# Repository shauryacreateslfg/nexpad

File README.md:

# nexpad
This was my first time working on hardware and glad i chose a macropad :) [it wasnt easy tho;) ]

# motive
i started with a hackpad because its usually every beginners first project but i didnt blindly use the guide, i worked upon adding more switches and customized functioning keys too myself,it was a hassle but i managed to do it on my OWN ;)
# nexpad's schematic and pcb
<h3>Schematic</h3>

<h3>PCB</h3>

<h3>3D view</h3>

# nexpad's Bill of Materials

| # | Part | Qty | Est. price (USD){incl. delivery} | Link |
|---|------|-----|---------------------------|------|
| 1 | Seed XIAO RP2040 | 1 | $8| https://robu.in/product/seeed-studio-xiao-rp2040-v1-0/ |
| 2 | MX-style switches(pack of 10) | 1 | $5 | https://meckeys.com/shop/accessories/keyboard-accessories/key-switches/cherry-mx-rgb-switch/ |
| 3 | 1N4148 diodes(pack of 50) | 1 | $1.72 | https://amzn.in/d/06aqwh1L |
| 4 | SK6812 MINI-E RGB LEDs | 10 | $0.226 | https://nanohertztechnologies.com/products/addressable-smd-led-sk6812mini-e-6812-ws2812-opsco |
| 5 | EC11 rotary encoder,20 mm | 1 | $3 | https://amzn.in/d/0gVF5ons |
| 6 | Encoder knob, 6mm D-shaft bore | 1 | $3 | https://3dprintshop.in/product/rotary-encoder-knob-set |
| 7 | 0.91" OLED 128x32 I2C (GND-VCC-SCL-SDA) | 1 | $4.5 | https://amzn.in/d/0hrdOsnR |
| 8 | Clear DSA keycaps(set of 5) | 2 | $1.75 | https://meckeys.com/shop/accessories/keyboard-accessories/keycaps/blank/blank-dsa-keycaps-1u/ |
| 9 | M3x16mm screws(pack of 25) | 1 | $3.13 |https://robu.in/product/easymech-ht-socket-button-head-cap-allen-bolt-m3-x-16-25-pcs/?gad_source=1&gad_campaignid=17416544847&gbraid=0AAAAADvLFWcknqAv5wyUr5iHjU1fO8vGA&gclid=Cj0KCQiAiJXYBhD_ARIsAAx2AHlxDKm8Cy3Y0g9CO__VHovhe8yq4j8NSwfvPJGNMKHT2k4CM0TFYrsaAh_LEALw_wcB|
| 10 | M3x5x4 heat-set inserts(pack of 25) | 1 | $2.3 | https://www.amazon.in/Yaocom-Threaded-Inserts-Printing-Components/dp/B0DG59PW2R |
| 11 | Custom 2-layer PCB | 1 | $27 | https://www.lioncircuits.com/quote?srsltid=AYCX9vJdAOgetnfsQttWt803HXfoI7JA8gKbzYeIGTpMUAf8BRxgDmF3 |
| 12 | 3D printed case, (base + bezel), printed by a friend | 1 | $10 | https://amzn.in/d/0f2i6nKE |
| 13 | 330 Ohm Resistor(pack of 20) | 1 | $1.7 | https://quartzcomponents.com/products/330-ohm-330-e-5-smd-resistor-0805-pack-of-20-pieces |
| 14 | Soldering Iron | 1 | $2.6 | https://www.amazon.in/Electronic-Spices-Black-Color-Soldering/dp/B0BNX3WZWJ |
| 15 | Soldering Iron Stand | 1 | $1.7 | https://amzn.in/d/0aQ20640 |
| 16 | Solder Wire 60/40, 50 g | 1 | $1.5 | https://amzn.in/d/07wNbBuL |
| 17 | Soldering Flux Paste, 15 g | 1 | $1.13 | https://amzn.in/d/0eGcyvb2 |
| 18 | Desoldering Wick, 1.5 m | 1 | $2.26 | https://www.amazon.in/UPTO-DATE-PRODUCTS-Desoldering-1-5mm-1-5Meter/dp/B0H62CXC13 |
||Total Cost (including delivery)| | $85-90||

#
made with love <3 
Shaurya

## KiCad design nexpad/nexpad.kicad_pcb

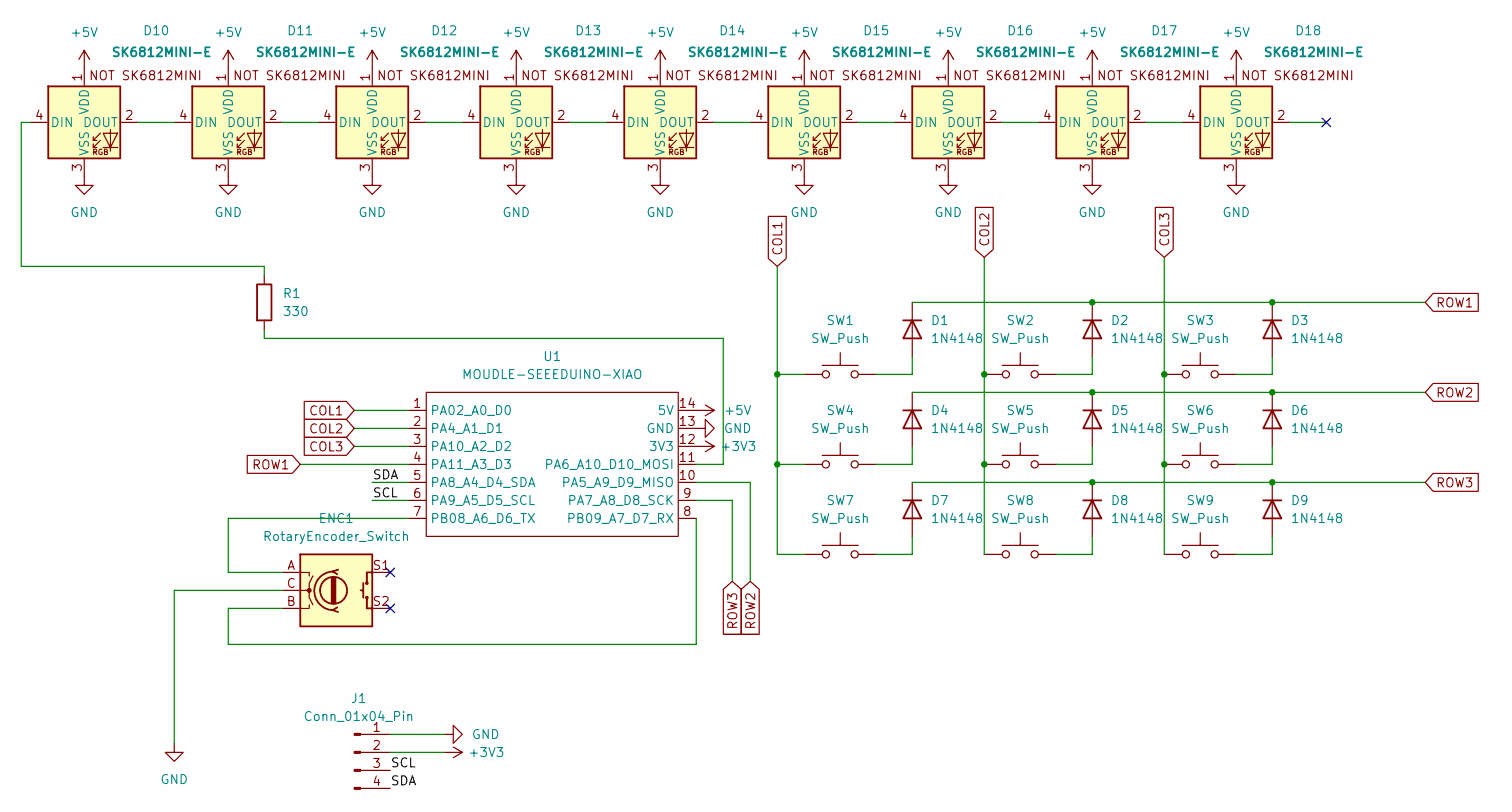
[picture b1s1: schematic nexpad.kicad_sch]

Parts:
D1, D2, D3, D4, D5, D6, D7, D8, D9: 1N4148; D_DO-35_SOD27_P7.62mm_Horizontal
D10, D11, D12, D13, D14, D15, D16, D17, D18: SK6812MINI-E; SK6812MINI-E_fixed
ENC1: RotaryEncoder_Switch; RotaryEncoder_Alps_EC11E-Switch_Vertical_H20mm
J1: Conn_01x04_Pin; SSD1306-0.91-OLED-4pin-128x32
R1: 330; R_0805_2012Metric
SW1, SW2, SW3, SW4, SW5, SW6, SW7, SW8, SW9: SW_Push; SW_Cherry_MX_1.00u_PCB
U1: MOUDLE-SEEEDUINO-XIAO; XIAO-Generic-Hybrid-14P-2.54-21X17.8MM

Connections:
+3V3: J1.2, U1.12 (3V3)
+5V: D10.1 (VDD), D11.1 (VDD), D12.1 (VDD), D13.1 (VDD), D14.1 (VDD), D15.1 (VDD), D16.1 (VDD), D17.1 (VDD), D18.1 (VDD), U1.14 (5V)
/SCL: J1.3, U1.6 (PA9_A5_D5_SCL)
/SDA: J1.4, U1.5 (PA8_A4_D4_SDA)
COL1: SW1.1, SW4.1, SW7.1, U1.1 (PA02_A0_D0)
COL2: SW2.1, SW5.1, SW8.1, U1.2 (PA4_A1_D1)
COL3: SW3.1, SW6.1, SW9.1, U1.3 (PA10_A2_D2)
GND: D10.3 (VSS), D11.3 (VSS), D12.3 (VSS), D13.3 (VSS), D14.3 (VSS), D15.3 (VSS), D16.3 (VSS), D17.3 (VSS), D18.3 (VSS), ENC1.C, J1.1, U1.13 (GND)
unnamed: D1.2 (A), SW1.2
unnamed: D2.2 (A), SW2.2
unnamed: D3.2 (A), SW3.2
unnamed: D4.2 (A), SW4.2
unnamed: D5.2 (A), SW5.2
unnamed: D6.2 (A), SW6.2
unnamed: D7.2 (A), SW7.2
unnamed: D8.2 (A), SW8.2
unnamed: D9.2 (A), SW9.2
unnamed: D10.4 (DIN), R1.1
unnamed: D10.2 (DOUT), D11.4 (DIN)
unnamed: D11.2 (DOUT), D12.4 (DIN)
unnamed: D12.2 (DOUT), D13.4 (DIN)
unnamed: D13.2 (DOUT), D14.4 (DIN)
unnamed: D14.2 (DOUT), D15.4 (DIN)
unnamed: D15.2 (DOUT), D16.4 (DIN)
unnamed: D16.2 (DOUT), D17.4 (DIN)
unnamed: D17.2 (DOUT), D18.4 (DIN)
unnamed: R1.2, U1.11 (PA6_A10_D10_MOSI)
unnamed: ENC1.A, U1.7 (PB08_A6_D6_TX)
unnamed: ENC1.B, U1.8 (PB09_A7_D7_RX)
ROW1: D1.1 (K), D2.1 (K), D3.1 (K), U1.4 (PA11_A3_D3)
ROW2: D4.1 (K), D5.1 (K), D6.1 (K), U1.10 (PA5_A9_D9_MISO)
ROW3: D7.1 (K), D8.1 (K), D9.1 (K), U1.9 (PA7_A8_D8_SCK)

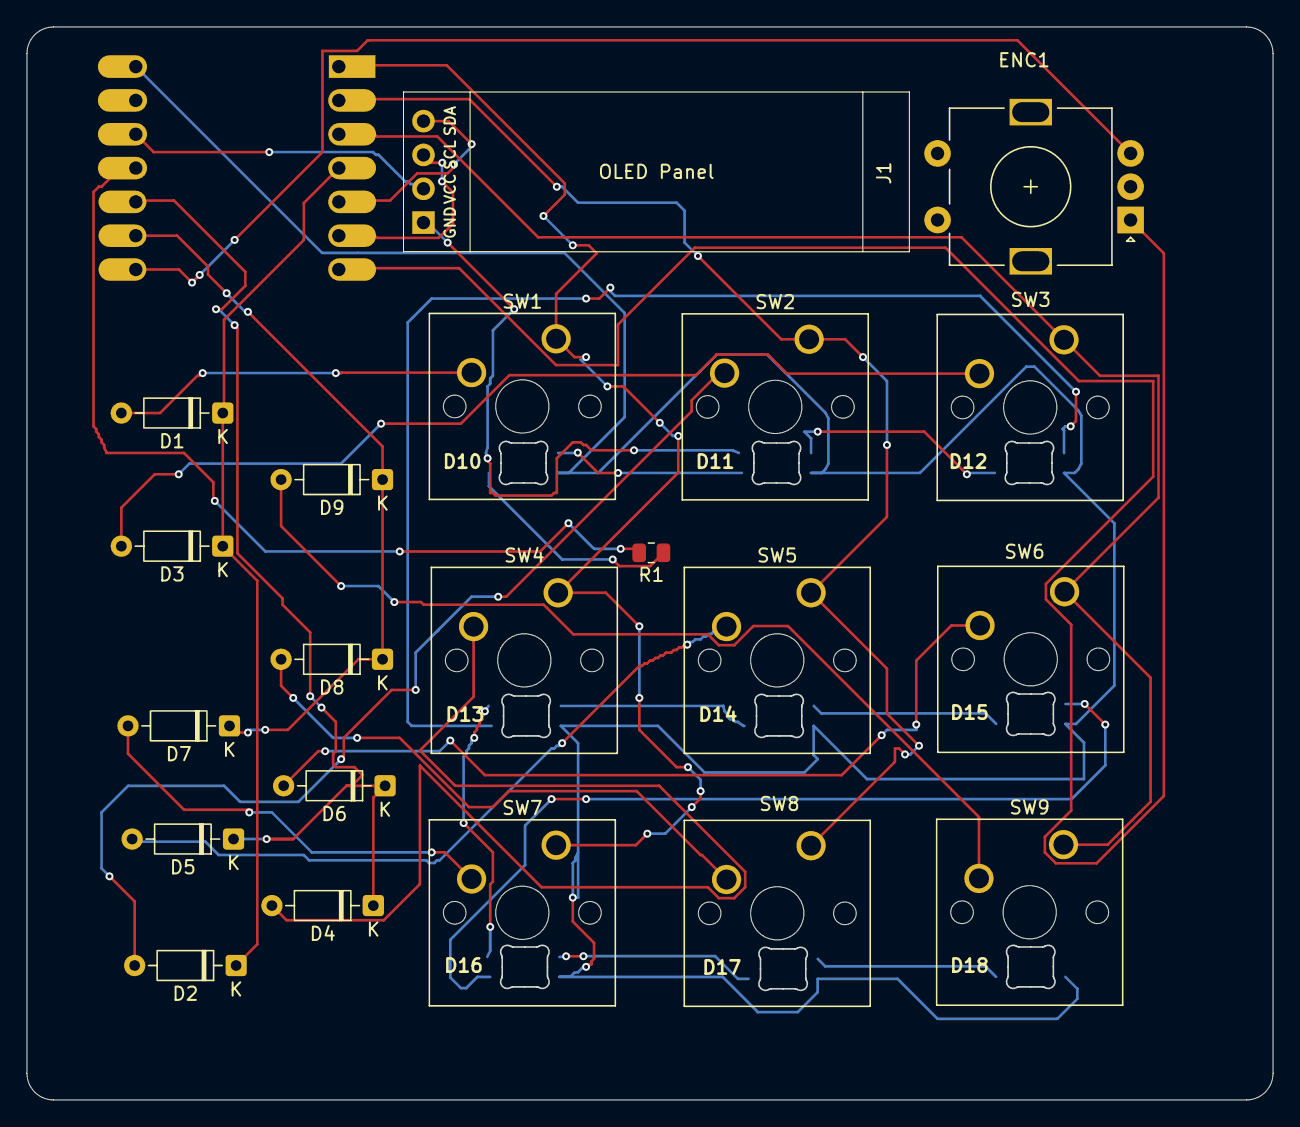
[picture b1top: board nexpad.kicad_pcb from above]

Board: 2 copper layers, 93.6 x 80.6 mm, 31 parts (1 on the bottom side), 32 nets.
